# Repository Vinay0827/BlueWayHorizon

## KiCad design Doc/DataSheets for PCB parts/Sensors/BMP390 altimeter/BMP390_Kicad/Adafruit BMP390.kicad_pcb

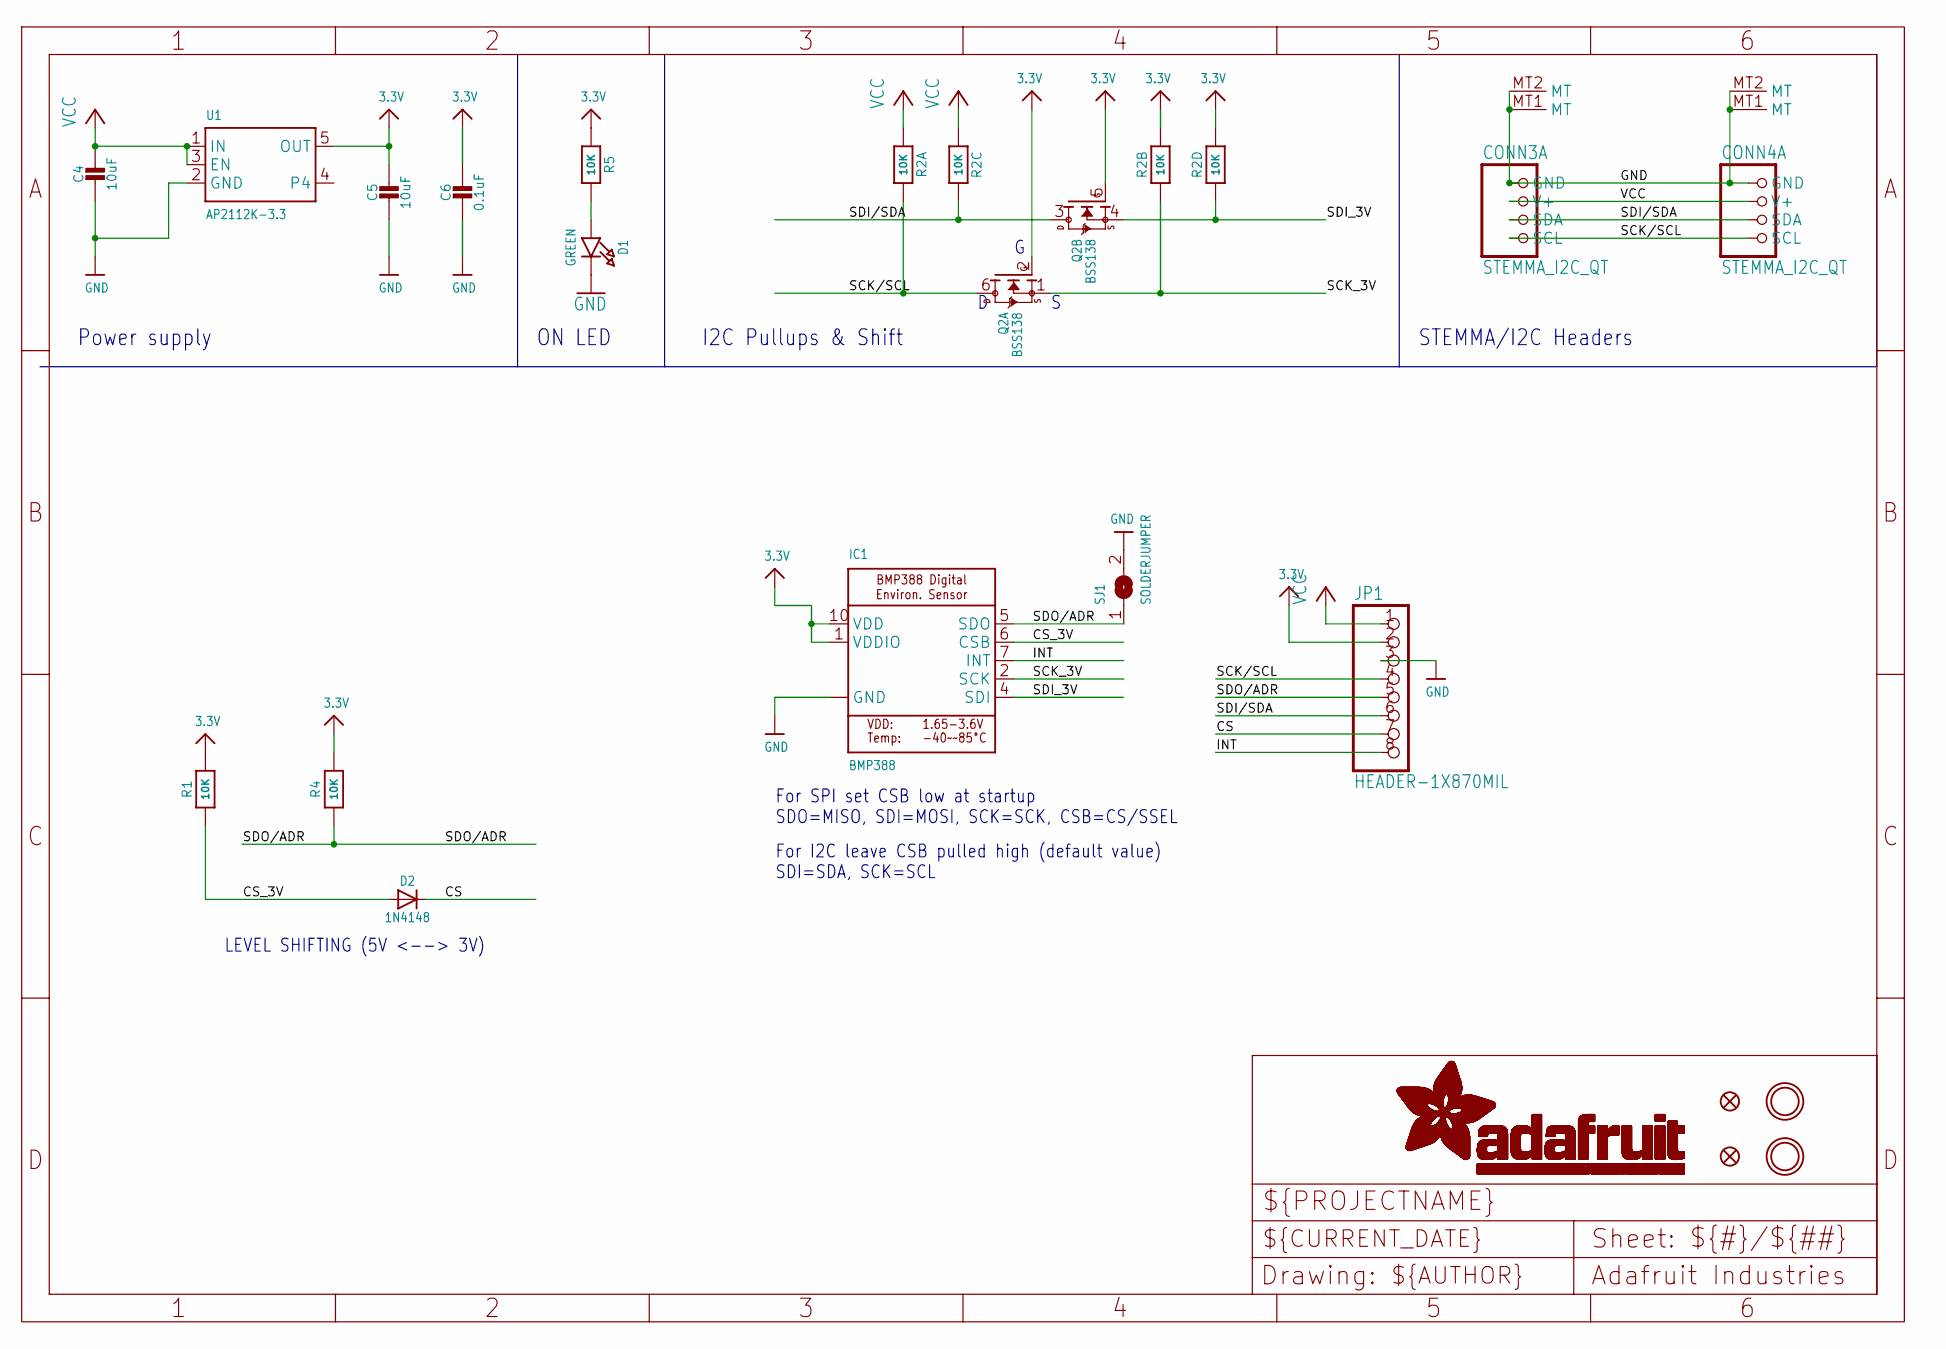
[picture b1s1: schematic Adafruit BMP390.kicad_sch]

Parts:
C4, C5: 10uF; 0805-NO
C6: 0.1uF; 0603-NO
CONN3, CONN4: STEMMA_I2C_QT; JST_SH4
D1: GREEN; CHIPLED_0603_NOOUTLINE
D2: 1N4148; SOD-323
FID3, FID4: FIDUCIAL_1MM
IC1: BMP388
JP1: HEADER-1X870MIL; 1X08_ROUND_70
Q2: BSS138; SOT363
R1, R4, R5: 10K; 0603-NO
R2: 10K; RESPACK_4X0603
SJ1: SOLDERJUMPER; SOLDERJUMPER_ARROW_NOPASTE
U1: AP2112K-3.3; SOT23-5
U$40, U$41: MOUNTINGHOLE2.5; MOUNTINGHOLE_2.5_PLATED

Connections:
3.3V: C5.1, C6.1, IC1.1 (VDDIO), IC1.10 (VDD), JP1.2, Q2.2 (G), Q2.5 (G), R1.2, R2.2 (1), R2.4 (1), R4.2, R5.1, U1.5 (OUT)
CS: D2.C, JP1.7
CS_3V: D2.A, IC1.6 (CSB), R1.1
GND: C4.2, C5.2, C6.2, CONN3.1 (GND), CONN3.MT1 (MT), CONN3.MT2 (MT), CONN4.1 (GND), CONN4.MT1 (MT), CONN4.MT2 (MT), D1.C, IC1.3 (GND), IC1.8 (GND), IC1.9 (GND), JP1.3, SJ1.2, U1.2 (GND)
INT: IC1.7 (INT), JP1.8
unnamed: D1.A, R5.2
SCK/SCL: CONN3.4 (SCL), CONN4.4 (SCL), JP1.4, Q2.6 (D), R2.8 (2)
SCK_3V: IC1.2 (SCK), Q2.1 (S), R2.7 (2)
SDI/SDA: CONN3.3 (SDA), CONN4.3 (SDA), JP1.6, Q2.3 (D), R2.6 (2)
SDI_3V: IC1.4 (SDI), Q2.4 (S), R2.5 (2)
SDO/ADR: IC1.5 (SDO), JP1.5, R4.1, SJ1.1
VCC: C4.1, CONN3.2 (V+), CONN4.2 (V+), JP1.1, R2.1, R2.3 (1), U1.1 (IN), U1.3 (EN)

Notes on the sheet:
Power supply
For I2C leave CSB pulled high (default value) SDI=SDA, SCK=SCL
For SPI set CSB low at startup SDO=MISO, SDI=MOSI, SCK=SCK, CSB=CS/SSEL
LEVEL SHIFTING (5V <--> 3V)
STEMMA/I2C Headers
ON LED
I2C Pullups & Shift

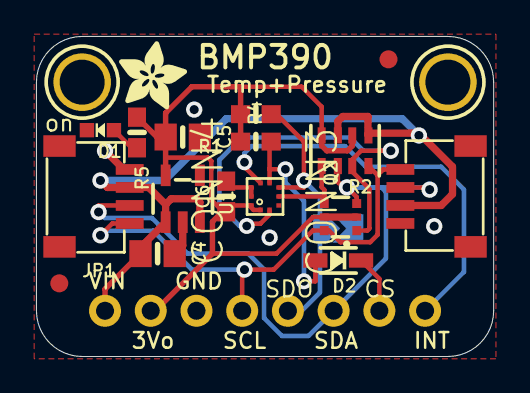
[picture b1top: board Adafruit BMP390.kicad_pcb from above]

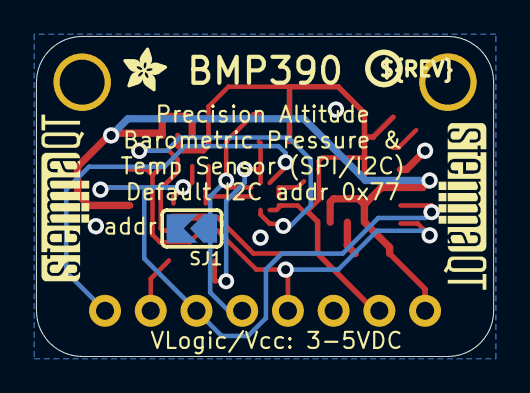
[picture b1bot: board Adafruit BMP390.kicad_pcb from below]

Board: 2 copper layers, 25.4 x 17.8 mm, 25 parts (5 on the bottom side), 12 nets.

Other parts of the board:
U$2: ADAFRUIT_2.5MM
U$46: ADAFRUIT_3.5MM
U$47: PCBFEAT-REV-040
U$48, U$49: STEMMAQT

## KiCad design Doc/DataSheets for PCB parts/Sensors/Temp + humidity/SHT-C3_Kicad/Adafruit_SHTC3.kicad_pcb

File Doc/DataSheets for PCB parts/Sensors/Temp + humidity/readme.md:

The Eagle board files can be found here 
https://github.com/adafruit/Adafruit-SHTC3-PCB

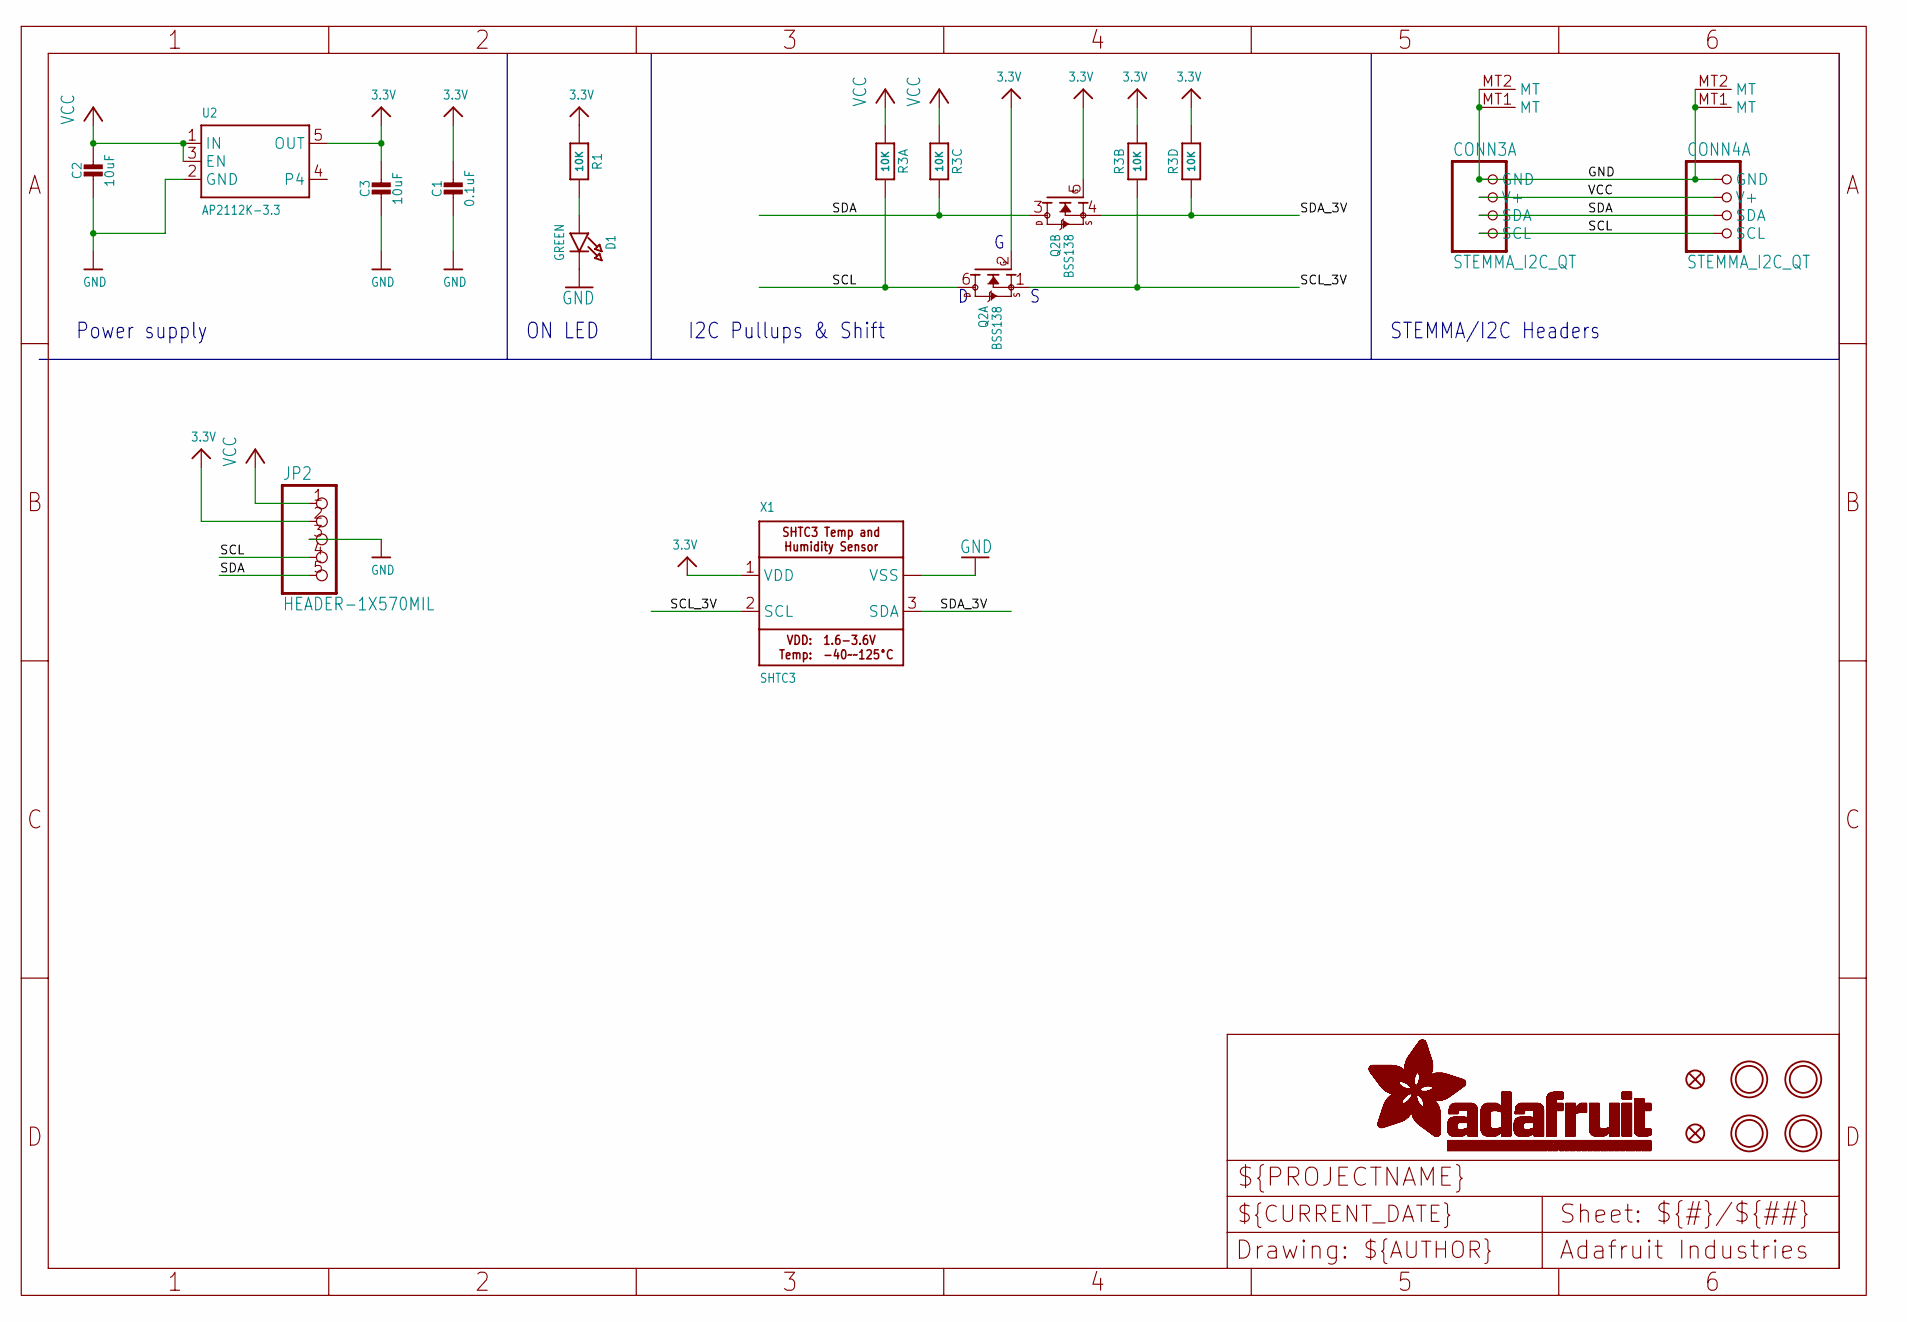
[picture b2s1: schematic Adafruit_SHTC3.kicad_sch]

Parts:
C1: 0.1uF; 0603-NO
C2, C3: 10uF; 0805-NO
CONN3, CONN4: STEMMA_I2C_QT; JST_SH4
D1: GREEN; CHIPLED_0603_NOOUTLINE
FID3, FID4: FIDUCIAL_1MM
JP2: HEADER-1X570MIL; 1X05_ROUND_70
Q2: BSS138; SOT363
R1: 10K; 0603-NO
R3: 10K; RESPACK_4X0603
U2: AP2112K-3.3; SOT23-5
U$1, U$17, U$19, U$21: MOUNTINGHOLE2.5; MOUNTINGHOLE_2.5_PLATED
X1: SHTC3

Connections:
3.3V: C1.1, C3.1, JP2.2, Q2.2 (G), Q2.5 (G), R1.1, R3.2 (1), R3.4 (1), U2.5 (OUT), X1.1 (VDD)
GND: C1.2, C2.2, C3.2, CONN3.1 (GND), CONN3.MT1 (MT), CONN3.MT2 (MT), CONN4.1 (GND), CONN4.MT1 (MT), CONN4.MT2 (MT), D1.C, JP2.3, U2.2 (GND), X1.4 (VSS), X1.MNT (VSS)
unnamed: D1.A, R1.2
SCL: CONN3.4 (SCL), CONN4.4 (SCL), JP2.4, Q2.6 (D), R3.8 (2)
SCL_3V: Q2.1 (S), R3.7 (2), X1.2 (SCL)
SDA: CONN3.3 (SDA), CONN4.3 (SDA), JP2.5, Q2.3 (D), R3.6 (2)
SDA_3V: Q2.4 (S), R3.5 (2), X1.3 (SDA)
VCC: C2.1, CONN3.2 (V+), CONN4.2 (V+), JP2.1, R3.1, R3.3 (1), U2.1 (IN), U2.3 (EN)

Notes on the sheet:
STEMMA/I2C Headers
I2C Pullups & Shift
ON LED
Power supply

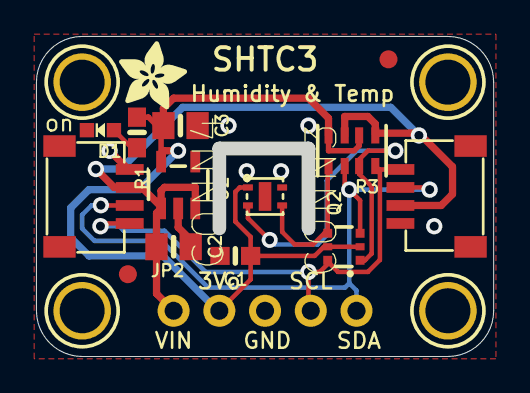
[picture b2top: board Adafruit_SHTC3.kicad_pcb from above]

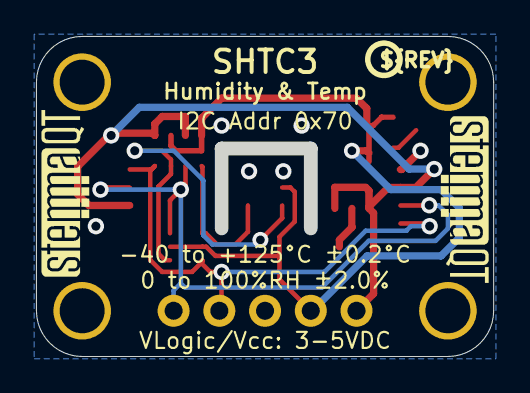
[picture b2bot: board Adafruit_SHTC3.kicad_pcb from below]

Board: 2 copper layers, 25.4 x 17.8 mm, 22 parts (3 on the bottom side), 8 nets.

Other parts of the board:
U$22: ADAFRUIT_3.5MM
U$25: PCBFEAT-REV-040
U$30, U$31: STEMMAQT

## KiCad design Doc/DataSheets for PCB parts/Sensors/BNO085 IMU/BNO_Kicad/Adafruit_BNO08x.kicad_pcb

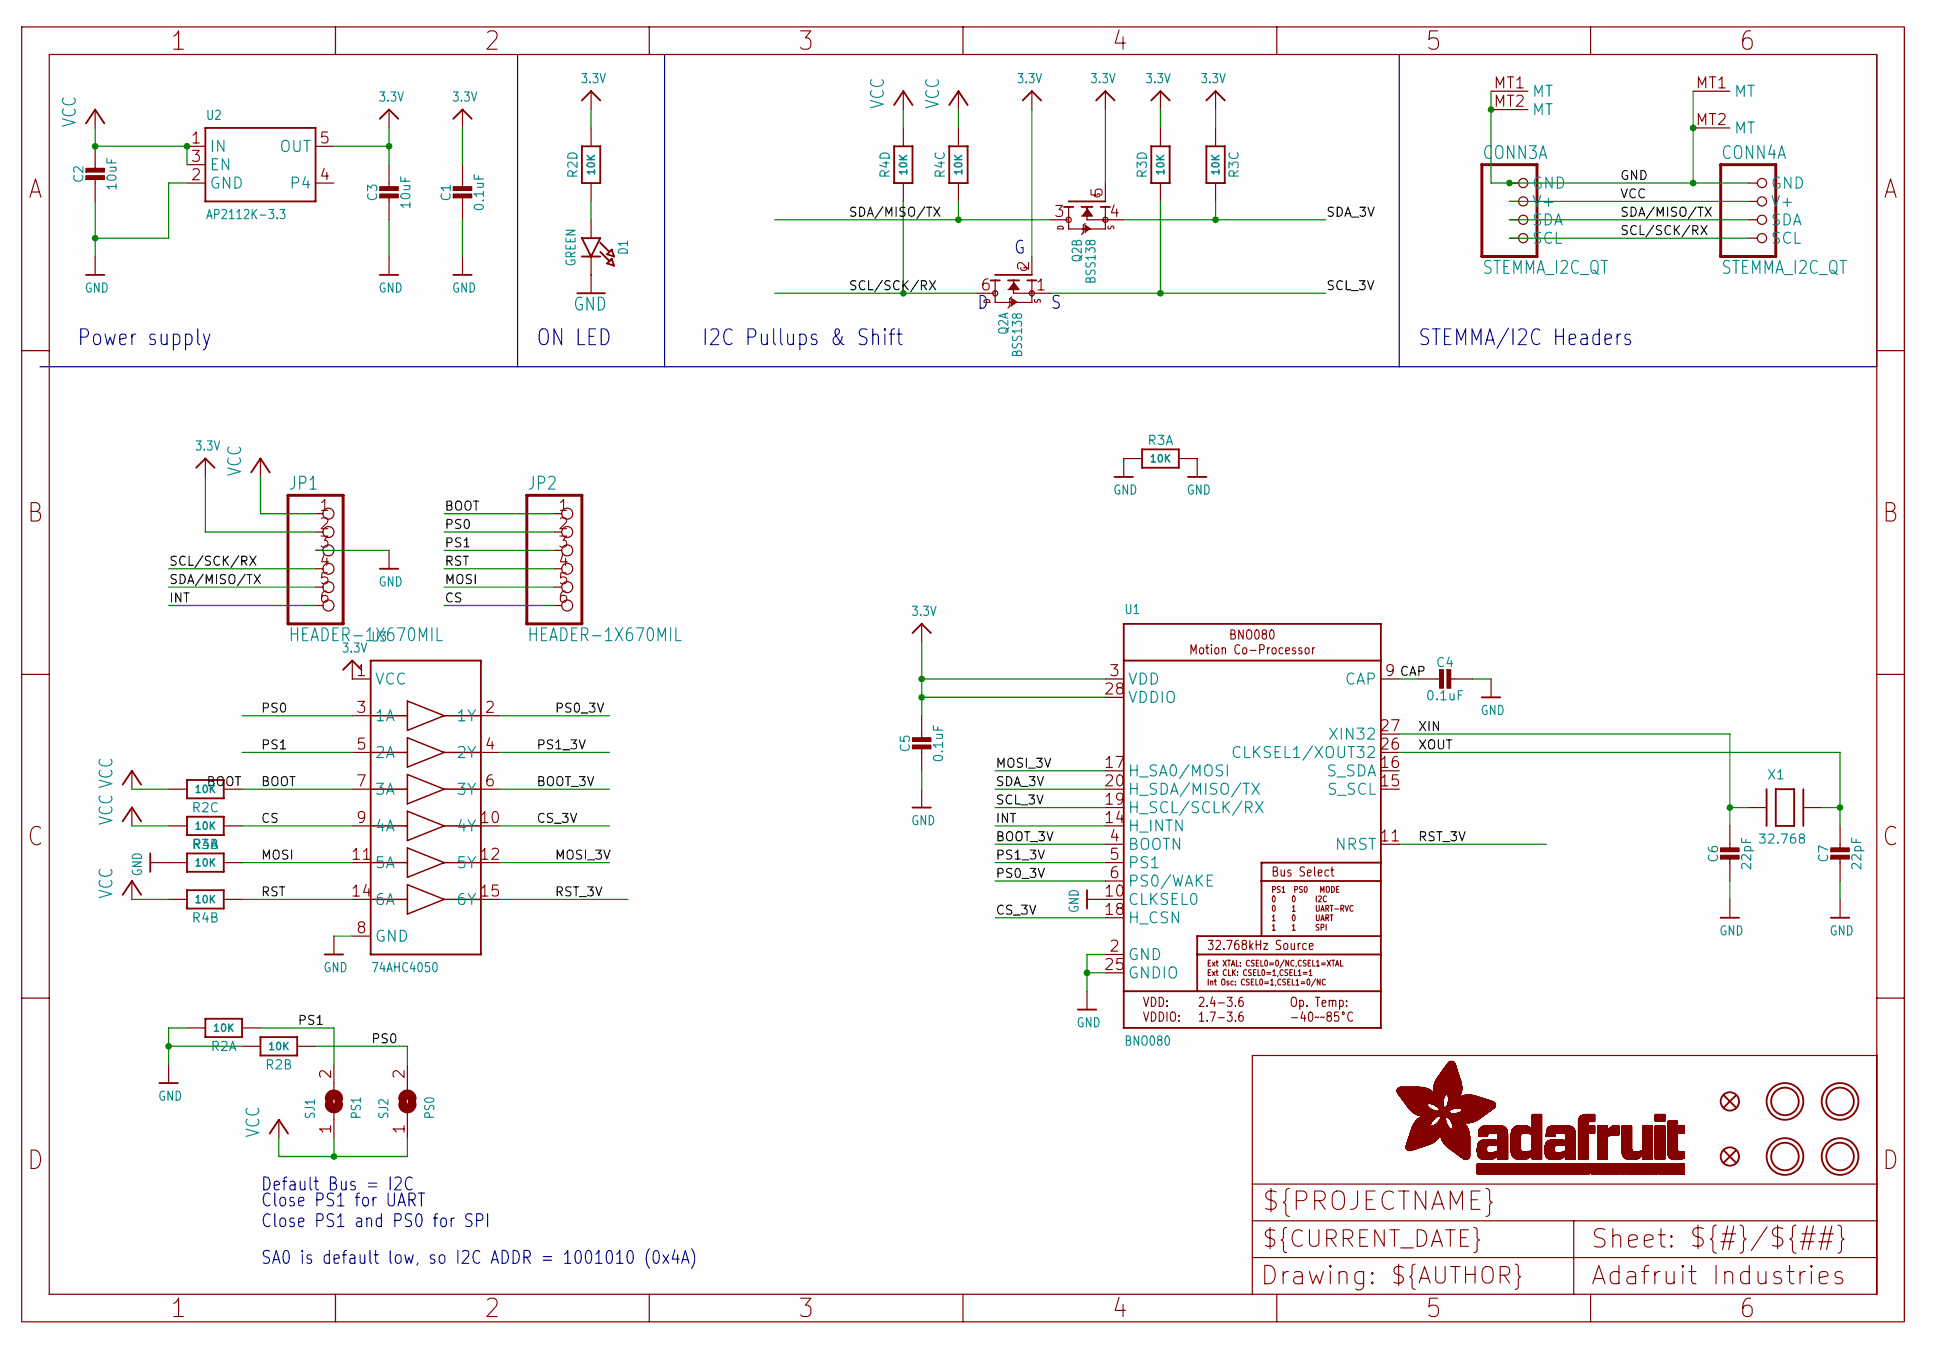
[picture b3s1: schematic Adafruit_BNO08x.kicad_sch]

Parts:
C1, C4, C5: 0.1uF; 0603-NO
C2, C3: 10uF; 0805-NO
C6, C7: 22pF; 0603-NO
CONN3, CONN4: STEMMA_I2C_QT; JST_SH4
D1: GREEN; CHIPLED_0603_NOOUTLINE
FID3, FID4: FIDUCIAL_1MM
JP1, JP2: HEADER-1X670MIL; 1X06_ROUND_70
Q2: BSS138; SOT363
R2, R3, R4: 10K; RESPACK_4X0603
SJ1: PS1; SOLDERJUMPER_ARROW_NOPASTE
SJ2: PS0; SOLDERJUMPER_ARROW_NOPASTE
U1: BNO080
U2: AP2112K-3.3; SOT23-5
U3: 74AHC4050; TSSOP16
U$1, U$17, U$19, U$21: MOUNTINGHOLE2.5; MOUNTINGHOLE_2.5_PLATED
X1: 32.768; XTAL3215

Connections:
3.3V: C1.1, C3.1, C5.1, JP1.2, Q2.2 (G), Q2.5 (G), R2.5 (2), R3.3 (1), R3.5 (2), U1.3 (VDD), U1.28 (VDDIO), U2.5 (OUT), U3.1 (VCC)
BOOT: JP2.1, R2.3 (1), U3.7 (3A)
BOOT_3V: U1.4 (BOOTN), U3.6 (3Y)
CAP: C4.2, U1.9 (CAP)
CS: JP2.6, R4.1, U3.9 (4A)
CS_3V: U1.18 (H_CSN), U3.10 (4Y)
GND: C1.2, C2.2, C3.2, C4.1, C5.2, C6.2, C7.2, CONN3.1 (GND), CONN3.MT1 (MT), CONN3.MT2 (MT), CONN4.1 (GND), CONN4.MT1 (MT), CONN4.MT2 (MT), D1.C, JP1.3, R2.7 (2), R2.8 (2), R3.1, R3.2 (1), R3.8 (2), U1.2 (GND), U1.10 (CLKSEL0), U1.25 (GNDIO), U2.2 (GND), U3.8 (GND)
INT: JP1.6, U1.14 (H_INTN)
MOSI: JP2.5, R3.7 (2), U3.11 (5A)
MOSI_3V: U1.17 (H_SA0/MOSI), U3.12 (5Y)
unnamed: D1.A, R2.4 (1)
PS0: JP2.2, R2.2 (1), SJ2.2, U3.3 (1A)
PS0_3V: U1.6 (PS0/WAKE), U3.2 (1Y)
PS1: JP2.3, R2.1, SJ1.2, U3.5 (2A)
PS1_3V: U1.5 (PS1), U3.4 (2Y)
RST: JP2.4, R4.2 (1), U3.14 (6A)
RST_3V: U1.11 (NRST), U3.15 (6Y)
SCL/SCK/RX: CONN3.4 (SCL), CONN4.4 (SCL), JP1.4, Q2.6 (D), R4.4 (1)
SCL_3V: Q2.1 (S), R3.4 (1), U1.19 (H_SCL/SCLK/RX)
SDA/MISO/TX: CONN3.3 (SDA), CONN4.3 (SDA), JP1.5, Q2.3 (D), R4.3 (1)
SDA_3V: Q2.4 (S), R3.6 (2), U1.20 (H_SDA/MISO/TX)
VCC: C2.1, CONN3.2 (V+), CONN4.2 (V+), JP1.1, R2.6 (2), R4.5 (2), R4.6 (2), R4.7 (2), R4.8 (2), SJ1.1, SJ2.1, U2.1 (IN), U2.3 (EN)
XIN: C6.1, U1.27 (XIN32), X1.P$1
XOUT: C7.1, U1.26 (CLKSEL1/XOUT32), X1.P$2

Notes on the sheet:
Power supply
Close PS1 for UART Close PS1 and PS0 for SPI
STEMMA/I2C Headers
ON LED
I2C Pullups & Shift
Default Bus = I2C
SA0 is default low, so I2C ADDR = 1001010 (0x4A)

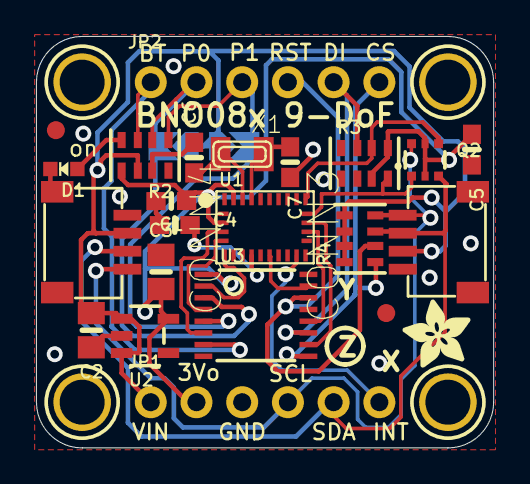
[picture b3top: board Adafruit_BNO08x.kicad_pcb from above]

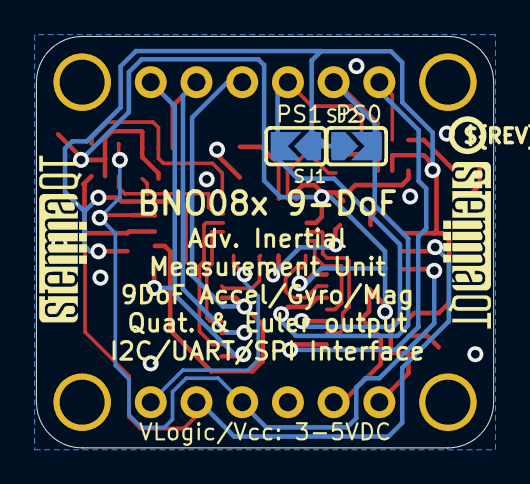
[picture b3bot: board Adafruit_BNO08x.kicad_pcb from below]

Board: 2 copper layers, 25.4 x 22.9 mm, 32 parts (5 on the bottom side), 24 nets.

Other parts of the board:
U$22: ADAFRUIT_3.5MM
U$25: PCBFEAT-REV-040
U$30, U$31: STEMMAQT

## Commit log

2026-03-01 The Doc has been updated
2026-03-01 PCB files has been added
2026-03-03 Added the important Docs with appropriate Readme and helper links
2026-03-03 the telemetry data has been added for sample and reference
2026-03-04 Dashboard has been upadted
2026-03-06 BNO085 Schematic updated
2026-03-06 Re-update Schematic BNO085
2026-03-07 SHT and BMP Added with LoRa Comm Module
